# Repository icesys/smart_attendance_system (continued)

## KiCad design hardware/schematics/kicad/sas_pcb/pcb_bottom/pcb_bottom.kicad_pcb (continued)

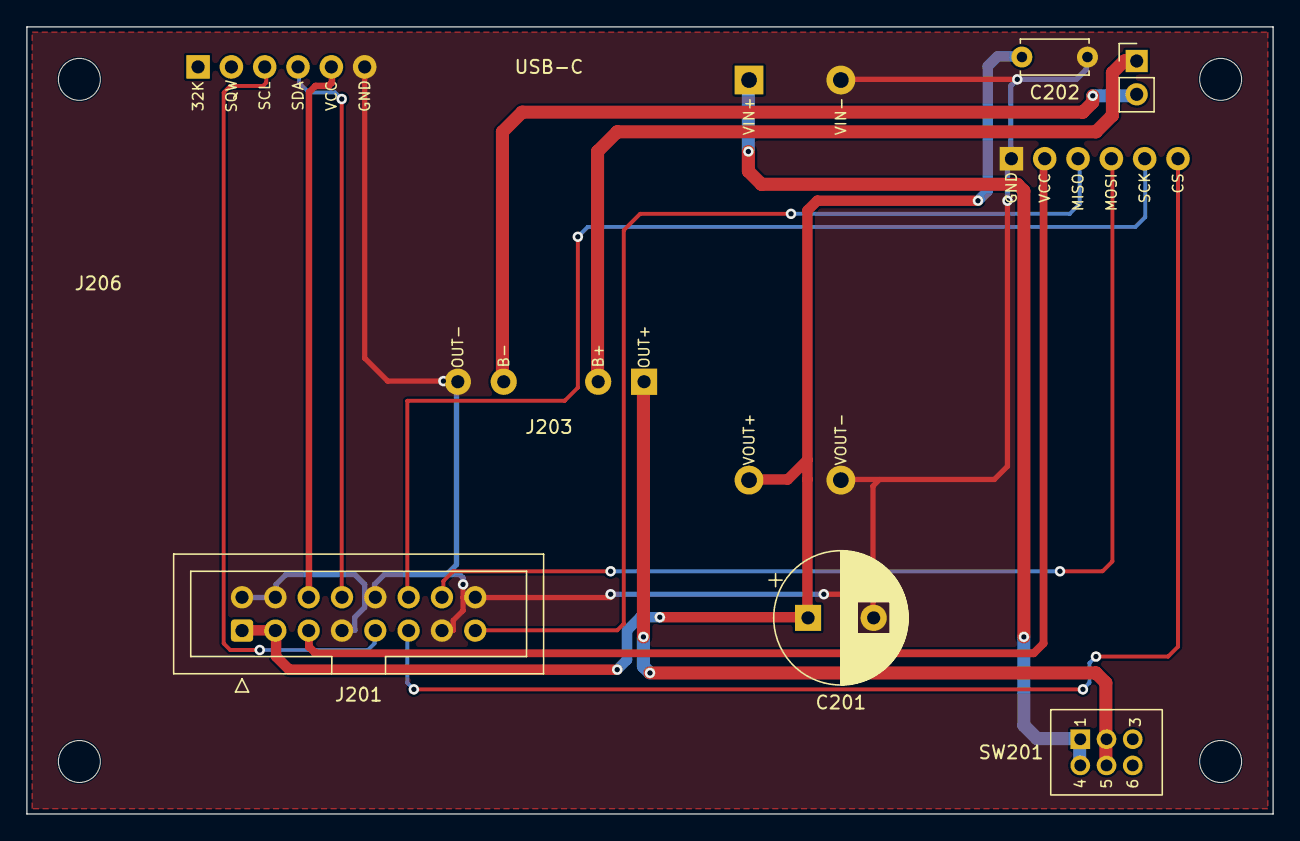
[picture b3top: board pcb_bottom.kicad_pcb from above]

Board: 2 copper layers, 95.0 x 60.0 mm, 13 parts (0 on the bottom side), 14 nets.

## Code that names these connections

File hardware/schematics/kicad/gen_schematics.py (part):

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

# ---------------- shared connector pin maps (same pinout at both ends of every cable) -------------
J_TM = {1: '3V3', 2: 'GND', 3: '5V_SYS', 4: 'GPIO42', 5: 'GPIO5', 6: 'GPIO1', 7: 'GPIO2', 8: 'GND',
        9: 'GPIO40', 10: 'GPIO41', 11: 'SCL', 12: 'SDA', 13: 'GND', 14: 'COIL_A', 15: 'COIL_B', 16: 'GND'}
J_MB = {1: '5V_BOOST', 2: 'GND', 3: '5V_BOOST', 4: 'GND', 5: '5V_SYS', 6: '3V3', 7: 'GND', 8: 'SDA',
        9: 'SCL', 10: 'GND', 11: 'SD_CS', 12: 'SD_SCK', 13: 'GND', 14: 'SD_MOSI', 15: 'SD_MISO', 16: 'GND'}
IDC = 'Connector_IDC:IDC-Header_2x08_P2.54mm_Vertical'
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    sh = Sheet('top', 'TOP board: LEDs, buzzer, buttons, OLED, RFID coil', 'J1 = J_TM cable to the MIDDLE board')
    sh.text('TOP BOARD (95 x 60 mm): LEDs and decoupling on the left, buzzer on the right, OLED and coil below', 140, 22, 2.5)
    conn2x8(sh, 'J1', 60, 150, J_TM, 'J_TM (to MIDDLE)')
    for i, (d, r, gpio, net, col) in enumerate([('D1', 'R1', 'GPIO5', 'LED_BLUE', 'blue (power LED)'),
                                                 ('D2', 'R2', 'GPIO1', 'LED_GRN', 'green'),
                                                 ('D3', 'R3', 'GPIO2', 'LED_RED', 'red')]):
        x = 130 + 30 * i
        sh.place('Device', 'LED', d, col, x, 50, rot=270, fp='LED_THT:LED_D5.0mm', nets={'K': 'GND', 'A': net})
        sh.place('Device', 'R', r, '220', x, 80, fp=RES, nets={1: net, 2: gpio})
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             nets={'K': 'BUZ_VCC', 'A': 'BUZ_N'})
    sh.place('Device', 'Q_NPN_EBC', 'Q1', '2N2222A', 365, 135, fp='Package_TO_SOT_THT:TO-92_Inline',
             nets={'B': 'BUZ_B', 'C': 'BUZ_N', 'E': 'GND'})
    sh.place('Device', 'R', 'R4', '1k', 300, 135, rot=90, fp=RES, nets={1: 'GPIO42', 2: 'BUZ_B'})
    sh.place('Device', 'R', 'R5', '100k', 320, 165, fp=RES, nets={1: 'BUZ_B', 2: 'GND'})
    sh.place('Switch', 'SW_Push', 'SW1', 'Button 1 (session)', 140, 205, fp='Button_Switch_THT:SW_PUSH_6mm',
             nets={1: 'GPIO40', 2: 'GND'})
    sh.place('Switch', 'SW_Push', 'SW2', 'Button 2 (info)', 140, 230, fp='Button_Switch_THT:SW_PUSH_6mm',
             nets={1: 'GPIO41', 2: 'GND'})
    sh.place('Connector_Generic', 'Conn_01x04', 'J2', 'OLED 0.96in (GND VCC SCL SDA)', 250, 195,
             fp='smart_attendance:MOD_OLED096', nets={1: 'GND', 2: '3V3', 3: 'SCL', 4: 'SDA'})
    sh.place('Connector_Generic', 'Conn_01x02', 'J3', 'RFID coil 35 x 46', 250, 235, fp=HDR % 2,
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

ESP_L = ['GND', 'GND', 'GPIO19', 'GPIO20', 'GPIO21', 'GPIO47', 'GPIO48', 'GPIO45', 'GPIO0', 'GPIO35', 'GPIO36',
         'GPIO37', 'GPIO38', 'GPIO39', 'GPIO40', 'GPIO41', 'GPIO42', 'GPIO2', 'GPIO1', 'RX', 'TX', 'GND']
ESP_R = ['GND', '5V', 'GPIO14', 'GPIO13', 'GPIO12', 'GPIO11', 'GPIO10', 'GPIO9', 'GPIO46', 'GPIO3', 'GPIO8',
         'GPIO18', 'GPIO17', 'GPIO16', 'GPIO15', 'GPIO7', 'GPIO6', 'GPIO5', 'GPIO4', 'RST', '3V3', '3V3']
ESP_USED = {'GND': 'GND', '5V': '5V_SYS', '3V3': '3V3', 'GPIO40': 'GPIO40', 'GPIO41': 'GPIO41', 'GPIO42': 'GPIO42',
            'GPIO2': 'GPIO2', 'GPIO1': 'GPIO1', 'GPIO5': 'GPIO5', 'GPIO8': 'SCL', 'GPIO9': 'SDA',
            'GPIO10': 'SD_CS', 'GPIO11': 'SD_SCK', 'GPIO12': 'SD_MOSI', 'GPIO13': 'SD_MISO', 'GPIO18': 'GPIO18'}


def esp_nets(names):
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    for i, (c, v, n) in enumerate([('C1', '10u', '5V_SYS'), ('C2', '100n', '5V_SYS'), ('C3', '100n', '3V3')]):
        sh.place('Device', 'C', c, v, 290 + 17 * i, 90, fp=CER, nets={1: n, 2: 'GND'})
    sh.place('Connector_Generic', 'Conn_01x05', 'J3', 'RDM6300 header 1 (TX RX nc GND 5V)', 290, 175,
             fp='Connector_PinSocket_2.54mm:PinSocket_1x05_P2.54mm_Vertical', nets={1: 'GPIO18', 4: 'GND', 5: '5V_SYS'}, nc=[2, 3])
    sh.place('Connector_Generic', 'Conn_01x02', 'J4', 'RDM6300 antenna', 290, 225,
             fp='Connector_PinSocket_2.54mm:PinSocket_1x02_P2.54mm_Vertical', nets={1: 'COIL_A', 2: 'COIL_B'})
    conn2x8(sh, 'J6', 380, 130, J_MB, 'J_MB (to BOTTOM)')
    sh.text('RDM6300 TX is 3.2 V: it goes straight to GPIO18 (no resistor needed)', 290, 200)
    sh.text('GPIO map: 1 green LED, 2 red LED, 5 blue LED, 8 SCL, 9 SDA, 10-13 SD, 18 RFID TX, 40/41 buttons, 42 buzzer', 20, 270)
    sh.finish(out)
    return sh
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    sh.text('BOTTOM BOARD (95 x 60 mm): the 18650 holder sits UNDER this board, its two wires come up to J2', 150, 22, 2.5)
    conn2x8(sh, 'J1', 60, 150, J_MB, 'J_MB (to MIDDLE)')
    sh.place('Connector_Generic', 'Conn_01x06', 'J5', 'microSD module (GND VCC MISO MOSI SCK CS)', 160, 50,
             fp='smart_attendance:MOD_SD_6PIN', nets={1: 'GND', 2: '5V_SYS', 3: 'SD_MISO', 4: 'SD_MOSI', 5: 'SD_SCK', 6: 'SD_CS'})
    sh.place('Connector_Generic', 'Conn_01x06', 'J6', 'DS3231 (32K SQW SCL SDA VCC GND)', 260, 50,
             fp='smart_attendance:MOD_DS3231_6PIN', nets={3: 'SCL', 4: 'SDA', 5: '3V3', 6: 'GND'}, nc=[1, 2])
    sh.place('Switch', 'SW_DPDT_x2', 'SW1', 'Slide switch 6-pin', 160, 110, unit=1, fp='smart_attendance:SW_Slide_6pin_2mm',
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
